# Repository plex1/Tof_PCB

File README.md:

# Time-of-Flight (ToF) PCB 

Contains optical transceiver for lidar or optical communication applications.

Laser diode options:
-  OPV310
-  SPL90 (not extensively tested)
   - Mods required: The A version of the NCP81074A of the MOSFET driver should be used. The supply voltage for the Mosfet driver should be increased from 5V to 12V. The peak power can be considerably increased with a higher voltage and lower shunt resistor value. In this case the duty cycle should be increased correspondingly for eye safety.

Photo diodes options:
- MTAPD-06-013
- SiPM MICRORB-10020-MLP-TR1

## Libraries

Uses the following libraries:
- KiCad Symbol Library: [ioda_symbols](https://github.com/plex1/ioda_symbols)
- KiCad Footprint Library: [ioda_footprints](https://github.com/plex1/ioda_footprints)

## Image

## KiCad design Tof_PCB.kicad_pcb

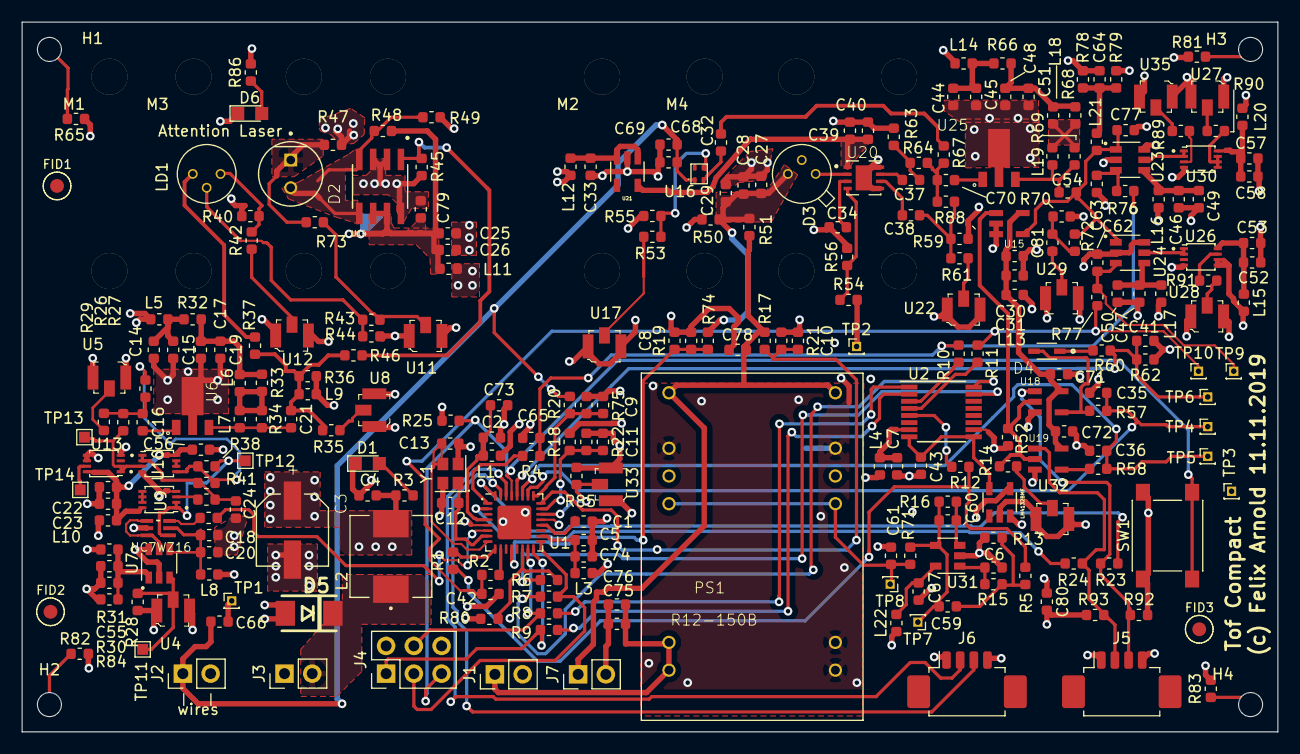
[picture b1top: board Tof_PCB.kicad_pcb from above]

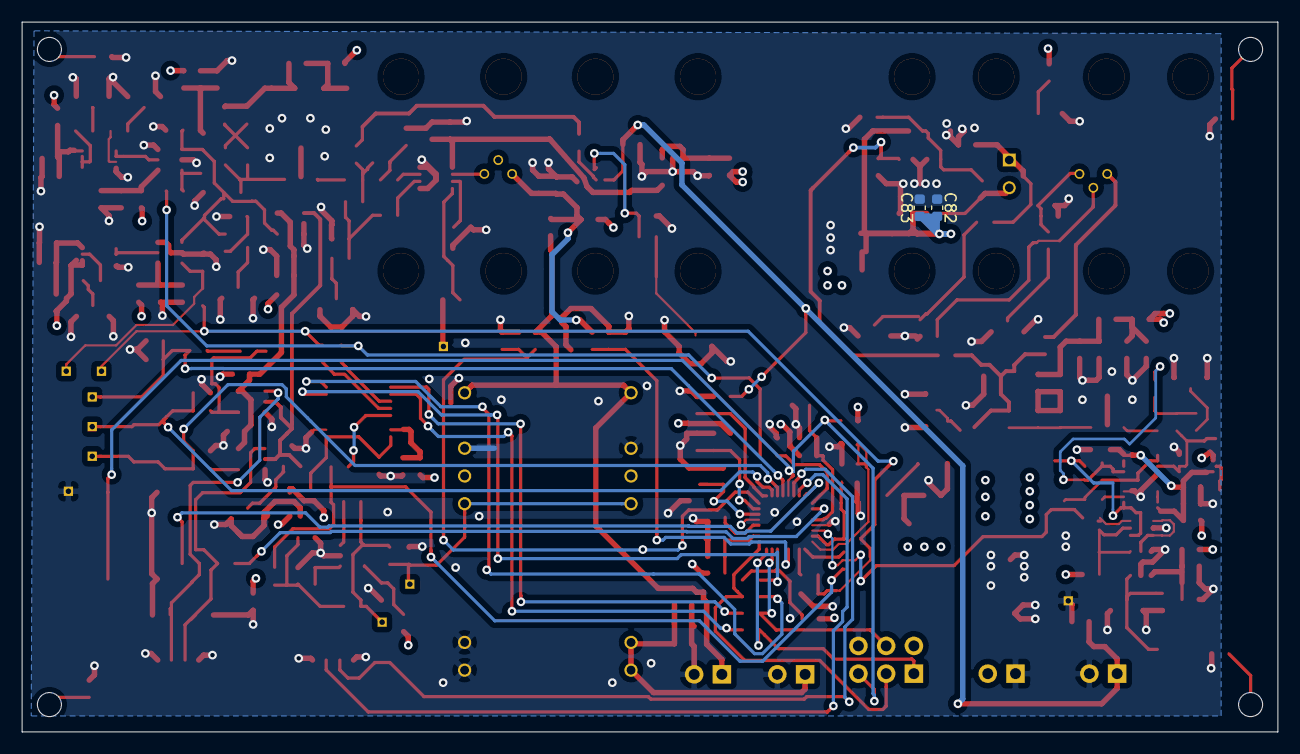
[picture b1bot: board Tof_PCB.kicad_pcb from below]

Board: 4 copper layers, 115.0 x 65.0 mm, 275 parts (2 on the bottom side), 135 nets.

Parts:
C1, C2, C5, C6, C7, C15, C18, C19, C23, C26, C30, C40, C43, C45, C46, C47, C51, C53, C56, C58, C59, C60, C61, C62, C63, C64, C67, C69, C72, C82: 100nF; C_0603_1608Metric
C3: 100uF; CAPAE660X800N
C4, C8, C9, C10, C11, C14, C16, C17, C20, C21, C22, C25, C31, C32, C33, C34, C35, C36, C37, C38, C39, C41, C42, C44, C48, C49, C50, C52, C54, C55, C57, C65, C66, C68, C70, C71, C73, C74, C75, C76, C79, C80, C81, C83: 2.2uF; C_0603_1608Metric
C12, C13: 16pF; C_0603_1608Metric
C24: c_tx_filt; C_0603_1608Metric
C27, C28, C29, C78: 10nF, 250V; C_0603_1608Metric
C77: c_rf_filt; C_0603_1608Metric
D1, D6: LED; LED_0805
D2: SPL_PL90; LEDRD254W40D590H700
D3: MTAPD-06
D4: BAS170W; SOD2513X114N
D5: SMBJ6.0A; DO214AA_1(K)-2(A)
FID1, FID2, FID3: Fiducial; MF_Aesthetics-FIDUCIAL_100MIL
H1, H2, H3, H4: MountingHole_Pad; MountingHole_2.2mm_M2
J1, J2, J3, J7: Screw_Terminal_01x02; ScrewTerminal_1x02_P2.54mm_Vertical
J4: Conn_02x03_Odd_Even; PinHeader_2x03_P2.54mm_Vertical
J5, J6: Conn_01x04; Molex_PicoBlade_53261-0471_1x04-1MP_P1.25mm_Horizontal
L1, L3, L4, L5, L8, L10, L11, L12, L13, L14, L15, L16, L17, L20, L22: bead; L_0603_1608Metric
L2: 6.8u; INDP7373X46N
L6, L7, L9, L18, L19, L21: 10uH; L_0603_1608Metric
LD1: OPV310; opv310
M1, M2, M3, M4: mounting_holes_laser; mounting_holes_17.8mm
PS1: R12-150B; RECOM_CONV_R12-150B
R1, R6, R7, R8, R9, R10, R11, R12, R23, R24, R26, R27, R37, R38, R39, R41, R46, R50, R65, R67, R81, R82, R83, R87, R88: 0R; R_0603_1608Metric
R2, R3, R4, R13, R30, R31, R84: 2.2k; R_0603_1608Metric
R5, R15, R18, R19, R20, R21, R22, R25, R33, R34, R54, R56, R57, R58, R60, R68, R69, R71, R80, R92, R93: 10k; R_0603_1608Metric
R14, R29, R35, R42, R43, R55, R61, R72, R73, R78, R79, R86: 200R; R_0603_1608Metric
R16, R40, R44: 100R; R_0603_1608Metric
R17, R51, R74: 1M; R_0603_1608Metric
R28, R36, R45, R52, R53, R70, R85: 50R; R_0603_1608Metric
R32, R66: 1.8R; R_0603_1608Metric
R47: 4.7R; R_0603_1608Metric
R48, R49: open; R_0603_1608Metric
R59, R63: 75R; R_0603_1608Metric
R62, R75, R76, R77: 100k; R_0603_1608Metric
R64, R89, R90, R91: 22R; R_0603_1608Metric
SW1: SW_Push; SW_Push_1P1T_NO_6x6mm_H9.5mm
TP1, TP2, TP3, TP4, TP5, TP6, TP7, TP8, TP9, TP10: TestPoint; PinHeader_1x01_P1.00mm_Vertical
TP11, TP12, TP13, TP14: TestPoint; TestPoint_Pad_1.0x1.0mm
U1: ATmega328PB-MU; QFN-32-1EP_5x5mm_P0.5mm_EP3.1x3.1mm
U2: DAC128S085; TSSOP-16_4.4x5mm_P0.65mm
U3: LM4132BMF; SOT95P280X145-5N
U4, U5, U8, U11, U12, U17, U22, U27, U28, U29, U32, U33, U35: UMCC_50Ohm; Molex_734120114_UMC_RF_CONN_Vertical
U6, U25: HMC589AST89E; SOT150P410X160-3N
U7, U23, U24: TLV3501; SOT-23-6
U9, U10, U13, U26, U30: NC7WZ00K8X; VSSOP-8_2.4x2.1mm_P0.5mm
U14: NCP81074BDR2G; SOIC-8-127P600X175-8N
U15: LMH6559MF; SOT95PX285X122-5N
U16: SiPM-MicroRB; CWDFN4_1.5x1.8_0.8P
U18, U19: ts5a4596; SOT95PX285X122-5N
U20: MAX40659; SON65P300X300X80-9N
U21: LP5907MFX-3.3_NOPB; SOT95P280X145-5N
U31: LM321; SOT-23-5
U34: NC7WZ16; SOT65P210X110-6N
Y1: Crystal_GND24; Crystal_SMD_2520-4Pin_2.5x2.0mm

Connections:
+5V: C3.1, C4.1, C80.1, J4.2, L1.2, L2.2, L3.1, L4.1, L5.2, L8.1, L10.2, L11.2, L12.2, L13.1, L14.2, L15.2, L16.1, L17.1, L20.2, L22.1, R3.2, R18.2, R25.1, R31.1, R50.1, R79.1, R80.1, R86.2, U3.3, U3.4, U13.5, U13.6, U26.5, U26.6
/5V_in: D5.1, J3.2, L2.1
/12V_in: C75.1, C76.1, J1.1, PS1.22, PS1.23
/MISO: J4.1, R9.2, U1.16
/MOSI: J4.4, R8.2, U1.15
/RXD: J6.2, U1.30
/SCK: J4.3, R7.2, U1.17
/TXD: J6.3, U1.31
/Tof Rx/3V3: C39.1, C40.1, U20.1, U21.5
/Tof Rx/TIA_out: C70.1, R64.1, R67.2, R88.2
/Tof Rx/buffer_out: R14.1, R52.2, U15.1, U18.2, U19.2
/Tof Rx/con: C38.2, R59.1, R61.2, R88.1
/Tof Rx/rfamp_out: C54.2, C77.1, C81.2, L21.1, U15.4, U23.1, U24.1
/Tof Rx/sipm_fastout: C32.2, R67.1
/Tof Rx/supply_lockin: C30.1, C31.1, C71.1, C72.1, L13.2, U15.5, U18.5, U19.5
/Tof Tx/LD_sense: R43.1, R73.2, U11.2
/Tof Tx/ld_driver_in: R45.2, R46.2, U14.1
/Tof Tx/ld_driver_supply: C25.1, C26.1, C79.1, C82.1, C83.1, L11.1, R48.2, U14.6, U14.7
/Tof Tx/pg_bypass: R26.2, R38.1, R41.1, U10.5
/Tof Tx/pulse_inv: R27.2, TP13.1, U10.3, U13.1, U13.2
/Tof Tx/start: R28.1, TP11.1, U4.2, U7.3
/Tof Tx/start_pulse: TP14.1, U13.7
/Tof Tx/start_th: U7.5, U34.1, U34.3
/Tof Tx/supply_inv1: C22.1, C23.1, C56.1, L10.1, U9.8, U10.8, U13.8
/Tof Tx/supply_th: C18.1, C20.1, L8.2, U7.4, U34.5
/Tof Tx/tx_amp_out: C21.2, L9.2, R35.2, R36.1, R37.2, R46.1
/V_5V_SENSE: C11.1, R18.1, R22.1, U1.23
/V_APD: C78.1, J7.1, PS1.12, PS1.13, R17.2, R51.1
/V_APD_R: C27.1, C28.1, C29.1, D3.2, R50.2, R51.2, R74.2
/V_APD_R_SENS: C8.1, R19.1, R74.1, U1.12
/V_APD_SENSE: C10.1, R17.1, R21.1, U1.24
/V_SiPM: C66.1, C68.1, C69.1, J2.1, R75.2, U16.1
/V_SiPM_SENSE: C9.1, R20.1, R75.1, U1.25
/V_adj_apd: R1.1, R5.2, R12.1
/V_adj_apd_filt: C61.1, PS1.8, PS1.17, R71.1, TP8.1
/XTAL1: C12.1, U1.7, Y1.1
/XTAL2: C13.1, U1.8, Y1.3
/comp_level_1: C65.1, R4.1, R10.1, R76.2
/comp_level_2: C42.1, R2.1, R11.1, R77.2, TP10.1
/lockin_1: J5.3, R23.1, R92.1, U18.1
/lockin_1_filt: C35.1, R57.1, TP4.1, U1.26
/lockin_1_mc: R23.2, U1.32
/lockin_1_peak: C41.1, R60.1, R62.2, TP6.1, U1.28
/lockin_2: J5.2, R24.1, R93.1, U19.1
/lockin_2_filt: C36.1, R58.1, TP5.1, U1.27
/lockin_2_mc: R24.2, U1.2
/start_mc: R87.2, U1.6
/stop_mc: R85.1, U1.22, U33.2
/~SS0: R6.2, R80.2, U1.14
/~reset: J4.5, R25.2, SW1.2, U1.29
GND: C1.2, C2.2, C3.2, C4.2, C5.2, C6.1, C7.2, C8.2, C9.2, C10.2, C11.2, C12.2, C13.2, C14.2, C15.2, C17.2, C18.2, C19.2, C20.2, C22.2, C23.2, C24.2, C25.2, C26.2, C27.2, C28.2, C29.2, C30.2, C31.2, C33.2, C34.2, C35.2, C36.2, C39.2, C40.2, C41.2, C42.2, C43.2, C44.2, C45.2, C46.2, C47.2, C48.2, C49.2, C50.2, C51.2, C52.2, C53.2, C55.2, C56.2, C57.2, C58.2, C61.2, C62.2, C63.2, C64.1, C65.2, C66.2, C67.2, C68.2, C69.2, C71.2, C72.2, C73.2, C74.2, C75.2, C76.2, C77.2, C78.2, C79.2, C80.2, C82.2, C83.2, D1.1, D5.2, D6.1, J1.2, J2.2, J3.1, J4.6, J5.1, J5.4, J6.1, J6.4, J7.2, L9.1, PS1.2, PS1.3, PS1.10, PS1.15, R13.1, R19.2, R20.2, R21.2, R22.2, R28.2, R30.2, R36.2, R40.1, R44.1, R45.1, R47.1, R49.1, R52.1, R53.2, R54.2, R56.2, R59.2, R62.1, R63.2, R65.2, R70.1, R78.2, R81.2, R82.2, R83.2, R84.2, R85.2, R92.2, R93.2, SW1.1, TP1.1, TP2.1, TP3.1, U1.5, U1.21, U1.33, U2.10, U3.2, U4.1, U4.3, U5.1, U5.3, U6.2, U7.2, U7.6, U8.1, U8.3, U9.4, U10.4, U11.1, U11.3, U12.1, U12.3, U13.4, U14.2, U14.3, U14.8, U15.2, U15.3, U17.1, U17.3, U18.3, U19.3, U20.5, U20.8, U20.9, U21.2, U22.1, U22.3, U23.2, U23.6, U24.2, U24.6, U25.2, U26.4, U27.1, U27.3, U28.1, U28.3, U29.1, U29.3, U30.4, U31.2, U32.1, U32.3, U33.1, U33.3, U34.2, U35.1, U35.3, Y1.2, Y1.4
unnamed: C1.1, U1.20
unnamed: C2.1, C73.1, L1.1, U1.4
unnamed: C5.1, C74.1, L3.2, U1.18
unnamed: C6.2, R15.1, U31.1
unnamed: C7.1, L4.2, U2.7
unnamed: C14.1, C15.1, L5.1, R32.2
unnamed: C16.1, R26.1, R27.1, R29.2
unnamed: C16.2, U6.1
unnamed: C17.1, C19.1, L6.1, R32.1, R33.1
unnamed: C21.1, L7.2, R34.2, U6.3
unnamed: C24.1, R39.1, R41.2, U10.1, U10.2
unnamed: C32.1, U16.2
unnamed: C33.1, L12.1, U21.1, U21.3
unnamed: C34.1, U20.3
unnamed: C37.1, U20.7
unnamed: C37.2, R63.1, R64.2
unnamed: C38.1, U20.6
unnamed: C43.1, U2.8, U2.9, U3.5
unnamed: C44.1, C45.1, L14.1, R66.2
unnamed: C46.1, C49.1, L16.2, U23.4
unnamed: C47.1, C50.1, L17.2, U24.4
unnamed: C48.1, C51.1, L18.1, R66.1, R68.1
unnamed: C52.1, C53.1, L15.1, U26.8
unnamed: C54.1, L19.2, R69.2, U25.3
unnamed: C55.1, R30.1, R31.2, R84.1, U7.1
unnamed: C57.1, C58.1, L20.1, U30.8
unnamed: C59.1, C60.1, R16.1, R71.2, TP7.1, U31.4
unnamed: C59.2, R5.1, R13.2, R15.2
unnamed: C60.2, R16.2, U31.3
unnamed: C62.1, R77.1, TP9.1, U24.3
unnamed: C63.1, R76.1, U23.3
unnamed: C64.2, L21.2, R78.1, R79.2
unnamed: C67.1, L22.2, U31.5
unnamed: C70.2, U25.1
unnamed: C81.1, R70.2, R72.1
unnamed: D1.2, R3.1
unnamed: D2.1, R47.2, R73.1
unnamed: D2.2, R48.1, R49.2, U14.4, U14.5
unnamed: D3.1, U20.2
unnamed: D4.1, R60.2
unnamed: D4.2, R57.2, U18.4
unnamed: D6.2, R86.1
unnamed: H1.1, R65.1
unnamed: H2.1, R82.1
unnamed: H3.1, R81.1
unnamed: H4.1, R83.1
unnamed: L6.2, L7.1, R33.2, R34.1
unnamed: L18.2, L19.1, R68.2, R69.1
unnamed: LD1.1, R37.1
unnamed: LD1.2, R43.2, R44.2
unnamed: LD1.3, R40.2, R42.2
unnamed: R1.2, U1.9
unnamed: R2.2, U1.10
unnamed: R4.2, U1.1
unnamed: R6.1, U2.15
unnamed: R7.1, U2.16
unnamed: R8.1, U2.1
unnamed: R9.1, U2.2
unnamed: R10.2, U2.3
unnamed: R11.2, U2.4
unnamed: R12.2, U2.5
unnamed: R14.2, U32.2
unnamed: R29.1, U5.2
unnamed: R35.1, U8.2
unnamed: R38.2, TP12.1, U9.1, U9.2, U34.4
unnamed: R39.2, U9.3
unnamed: R42.1, U12.2
unnamed: R53.1, R55.2, U16.3
unnamed: R54.1, R56.1, U20.4
unnamed: R55.1, U17.2
unnamed: R58.2, U19.4
unnamed: R61.1, U22.2
unnamed: R72.2, U29.2
unnamed: R87.1, U34.6
unnamed: R89.1, U35.2
unnamed: R89.2, U30.3
unnamed: R90.1, U27.2
unnamed: R90.2, U30.5, U30.6, U30.7
unnamed: R91.1, U28.2
unnamed: R91.2, U26.7
unnamed: U9.5, U9.6, U9.7
unnamed: U10.6, U10.7
unnamed: U23.5, U30.1, U30.2
unnamed: U24.5, U26.1, U26.2

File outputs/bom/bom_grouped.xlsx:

Ref | Qnty | Value | Footprint | Digi-Key_PN | Part PCBWay will supply | Comment
C1, C2, C5, C6, C7, C15, C18, C19, C23, C26, C30, C40, C43, C45, C46, C47, C51,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 | 29 | 100nF | Capacitor_SMD:C_0603_1608Metric | 490-3285-1-ND | GRM188R72A104KA35D
C3, | 1 | 100uF | IODA_Lib:CAPAE660X800N | PCE5024CT-ND | EEE-FTH101XAP
C4, C8, C9, C10, C11, C14, C16, C17, C20, C21, C22, C25, C31, C32, C33, C34, C3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 | 43 | 2.2uF | Capacitor_SMD:C_0603_1608Metric | 490-12740-1-ND | GRM188R61H225ME11D
C12, C13, | 2 | 16pF | Capacitor_SMD:C_0603_1608Metric | 399-7863-1-ND | C0603C160J5GACTU
C27, C28, C29, C78, | 4 | 10nF, 250V | Capacitor_SMD:C_0603_1608Metric | 732-12168-1-ND | 885342206006
D1, D6, | 2 | LED | LEDs:LED_0805 | 160-1423-1-ND | LTST-C171GKT
D4, | 1 | BAS170W | IODA_Lib:SOD2513X114N | BAS170WS-E3-08GICT-ND | BAS170WS-E3-08
D5, | 1 | SMBJ6.0A | OLIMEX_Diodes-FP:DO214AA_1(K)-2(A) | SMBJ6.0ABCT-ND | SMBJ6.0A
J1, J2, J3, J7, | 4 | Screw_Terminal_01x02 | IODA_Lib:ScrewTerminal_1x02_P2.54mm_Vertical | A98333-ND | 282834-2
J4, | 1 | Conn_02x03_Odd_Even | Connector_PinHeader_2.54mm:PinHeader_2x03_P2.54mm_Vertical | 609-3210-ND | 67996-206HLF | Part we will supply is substitute made in China.
J5, J6, | 2 | Conn_01x04 | Connector_Molex:Molex_PicoBlade_53261-0471_1x04-1MP_P1.25mm_Horizontal | WM7622CT-ND | 0532610471
L1, L3, L4, L5, L8, L10, L11, L12, L13, L14, L15, L16, L17, L20, L22, | 15 | bead | Inductor_SMD:L_0603_1608Metric | 490-5216-1-ND | BLM18HE152SN1D
L2, | 1 | 6.8uH | IODA_Lib:INDP7373X46N | 811-1180-1-ND | 46682C
L6, L7, L9, L18, L19, L21, | 6 | 10uH | Inductor_SMD:L_0603_1608Metric | 490-4025-1-ND | LQM18FN100M00D
R1, R6, R7, R8, R9, R23, R24, R27, R37, R39, | 10 | 0R | Resistor_SMD:R_0603_1608Metric | RMCF0603ZT0R00CT-ND | RMCF0603ZT0R00
R2, R3, R4, R13, R30, R31, R84, | 7 | 2.2k | Resistor_SMD:R_0603_1608Metric | RMCF0603FT2K20CT-ND | RMCF0603FT2K20
R5, R15, R18, R19, R20, R21, R22, R25, R33, R34, R54, R56, R57, R58, R60, R68, 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 | 21 | 10k | Resistor_SMD:R_0603_1608Metric | P10.0KHCT-ND | ERJ-3EKF1002V
R14, R29, R35, R42, R43, R55, R61, R72, R73, R78, R79, R86, | 12 | 200R | Resistor_SMD:R_0603_1608Metric | RHM200ADCT-ND | ESR03EZPF2000
R16, R40, R44, | 3 | 100R | Resistor_SMD:R_0603_1608Metric | RMCF0603FT100R | RMCF0603FT100R
R17, R51, R74, | 3 | 1M | Resistor_SMD:R_0603_1608Metric | 311-1.00MHRCT-ND | RC0603FR-071ML
R28, R45, R52, R53, R70, R85, | 6 | 50R | Resistor_SMD:R_0603_1608Metric | 541-56.0SCT-ND | CRCW060356R0FKEAHP
R32, R66, | 2 | 1.8R | Resistor_SMD:R_0603_1608Metric | 541-1.80CCCT-ND | CRCW08051R80FKEA
R47, | 1 | 4.7R | Resistor_SMD:R_0603_1608Metric | RNCP0603FTD4R70CT-ND | RNCP0603FTD4R70
R59, | 1 | 75R | Resistor_SMD:R_0603_1608Metric | RNCP0603FTD75R0CT-ND | RNCP0603FTD75R0
R62, R75, R76, R77, | 4 | 100k | Resistor_SMD:R_0603_1608Metric | RMCF0603FT110K | RMCF0603FT110K
R64, R89, R90, R91, | 4 | 22R | Resistor_SMD:R_0603_1608Metric | A129668CT-ND | CRGCQ0603F22R
TP1, TP2, TP3, TP4, TP5, TP6, TP7, TP8, TP9, TP10, | 10 | TestPoint | Connector_PinHeader_1.00mm:PinHeader_1x01_P1.00mm_Vertical | 732-5314-ND | 61300111121 | Part we will supply is substitute made in China.
U1, | 1 | ATmega328PB-MU | Package_DFN_QFN:QFN-32-1EP_5x5mm_P0.5mm_EP3.1x3.1mm | ATMEGA328PB-MURCT-ND | ATMEGA328PB-MUR
U4, U5, U8, U11, U12, U17, U22, U27, U28, U29, U32, U33, U35, | 13 | UMCC_50Ohm | IODA_Lib:Molex_734120114_UMC_RF_CONN_Vertical | A118077CT-ND | 1909763-1
U6, U25, | 2 | HMC589AST89E | IODA_Lib:SOT150P410X160-3N | 1127-3329-1-ND | HMC589AST89ETR
U7, U23, U24, | 3 | TLV3501 | IODA_Lib:SOT-23-6 | 296-43611-1-ND | TLV3501AIDR
U9, U10, U13, U26, U30, | 5 | NC7WZ00K8X | IODA_Lib:VSSOP-8_2.4x2.1mm_P0.5mm | NC7WZ00K8XCT-ND | NC7WZ00K8X
U14, | 1 | NCP81074BDR2G | IODA_Lib:SOIC-8-127P600X175-8N | NCP81074BDR2GOSCT-ND | NCP81074BDR2G
U15, | 1 | LMH6559MF | IODA_Lib:SOT95PX285X122-5N | 296-46123-1-ND | LMH6559MF
U18, U19, | 2 | ts5a4596 | IODA_Lib:SOT95PX285X122-5N | 296-17709-1-ND | TS5A4596DBVR
U20, | 1 | MAX40659 | IODA_Lib:SON65P300X300X80-9N | MAX40659ETA+TCT-ND | MAX40659ETA+T
U21, | 1 | LP5907MFX-3.3_NOPB | IODA_Lib:SOT95P280X145-5N | 296-38557-1-ND | LP5907MFX-3.3/NOPB
U31, | 1 | LM321 | Package_TO_SOT_SMD:SOT-23-5 | LM321MFX/NOPBCT-ND | LM321MFX/NOPB
U34, | 1 | NC7WZ16 | IODA_Lib:SOT65P210X110-6N | NC7WZ16P6XCT-ND | NC7WZ16P6X
Y1, | 1 | Crystal_GND24 | Crystal:Crystal_SMD_2520-4Pin_2.5x2.0mm | SER4068CT-ND | FA-20H 16.0000MF10Z-AJ0

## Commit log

2019-11-01 Initial commit (schematic + placement)
2019-11-06 Added RLC values
2019-11-07 Added more digikey numbers in BOM
2019-11-07 solved drc errors
2019-11-13 bugfixes
2019-11-15 Version 1.0. As ordered at PCBWay on 13.11.2019
2019-11-23 This is the actual pcb ordered by PCBWay 13.11.2019 The last commit had an error in the schematic files
    Revert "Version 1.0. As ordered at PCBWay on 13.11.2019"
    This reverts commit d90296e8e464a35f67a5ff7ebe731cf47d5f6555.
2019-11-25 changed 100k resistor and tlv3501 digikey numbers
2024-08-07 added schematics
2024-08-07 added 3d model
2024-08-14 added errata.txt
